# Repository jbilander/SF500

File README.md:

# SF500
Spitfire 500, A low-end 14 MHz Accelerator with IDE and 4/8 MB fast RAM for the Amiga 500.
***
Heavily inspired by Matthias Heinrichs' CDTV-RAM-IDE board. Many thanks to Matze for sharing his work and letting me open source this project.

https://gitlab.com/MHeinrichs/CDTV-RAM-IDE/

Please note, if you are going to build boards and sell for profit, you will need a consent from Matthias and also from Oliver Kastl if you are going to bundle this software http://aminet.net/package/disk/misc/oktapus with the hardware (ROM-chip).

***

    Board is four layers:
    
    signal (with 3V3-zone)
    power plane (GND)
    power plane (VCC)
    signal

***

Rev. 1B installed in an A500. The 7/14 MHz switch can be easily accessed if hanging out the sidecar port opening of the A500 case. This switch can also be switched while the machine is running.

***

***

Videos: <br /><br />
https://drive.google.com/file/d/1c2K9_kcEqxMMBJBd1aELfbt1fV5XXoU6/view?usp=sharing

SysInfo tests running _oktagon.device_ on WB 1.3 on KS 1.3: <br />
https://drive.google.com/file/d/1rewl8bivpIMPoLze_-Y7_mGYqzTiX6ET/view?usp=sharing

Cold boot running _oktagon.device_ and WB 1.3 on KS 1.3: <br />
https://drive.google.com/file/d/1MFdxnaCo8lNMqMQ6eJMtNUMSsBB8mtb-/view?usp=sharing

Cold boot running _scsi.device v109.3_  (oktapussy) and ClassicWB 3.1 (with 1.3 theme) on KS 3.1: <br />
https://drive.google.com/file/d/1IrmWWG6SJgc65BBj8jGnHebKbp6LAcYa/view?usp=sharing

***

The CPU and the speed-select switch clears the A500 keyboard nicely when installed. Also the CF- or SD-card adapter clears the ROM-chip nicely.

***

***

### Performance

14 MHz and JP3 Open (scsi.device v109.3):

<br />
<br />

14 MHz and JP3 Closed (oktagon.device v6.10):

***

Keep in mind Kickstart 1.3 does not have FFS (Fast File System) in ROM, 
so in order to use FFS with 1.3 make a small boot-partition (e.g. ~200 MB) and format it DOS\1, 
not International (DOS\3) or DirCache (DOS\5), and not OFS (DOS\0). For KS 3.1 I would format it FFS International (DOS\3) or perhaps use PFS3. <br /><br />
https://en.wikipedia.org/wiki/Amiga_Fast_File_System <br />

Also, do not forget to set the MaxTransfer to _0x1fe00_ and hit Enter button after typing, then save the setting. This applies to all versions except the new KS 3.2

<br />
<br />
Disk's partition and filesystem information should now be stored in the RDB (Rigid Disk Block)
for autoboot to work under WB 1.3 with oktagon.device. 
To install WB 1.3: Copy all content of the WB 1.3 floppy to the newly formatted Drive.

***

### How to Build:

The ROM image to burn to the AM29F040B-70JC chip can be downloaded from here: <br />
https://gitlab.com/MHeinrichs/CDTV-RAM-IDE/-/blob/master/Prog/ATOKTACOMBINED.rom-512.bin

The 64 KB ROM under _Releases_ is a combined ROM I made with the instructions from the textfile [EPROM-Hack_english.txt](https://github.com/jbilander/SF500/blob/main/EPROM-Hack_english.txt) in this repo (also available in German).
It is 060-compatible too, not that it makes any difference for this accelerator that uses a 68000 or 68010 CPU.

Burning any of the two ROM:s above will work with this Accelerator (SF500).

The last version of the Oktagon2008 from BSC is 6.12 - but still reports as 6.10. As far as I know, only the boot code has changed to be compatible with the 68060. The actual driver is still 6.10.

Remember to Program the chip BEFORE you solder it down to the PCB. Do not byteswap if you are using a TL866II-Plus or similar programmer on Windows/Intel-arch, these parts are 8-bit so there is no concept of byte swapping.

***

Soldering: Start with all the surface mounts and then TH. I usually start with the Voltage regulator and verify the 3V3. Then the CPLD and verify JTAG-connection, doing a boundary scan with ISE-Impact. No need to solder a pin header to the JTAG connector on the PCB, just hold the connector in position and press gently. It should also be possible to use a Raspberry Pi and the program _xc3sprog_. Optionally you can put 10k or 4.7k pull-ups on R10-R12 (TMS,TDI,TCK) if you have problems connecting to the CPLD, those are 3V3 pull-ups so shouldn't damage anything using GPIO from a RPi. VCC is +5V and can be supplied through a typical usb phone-charger or similar, check polarity BEFORE you plug it in.

***

<br />

***

Using some kapton tape can help to hold the chip in place while tacking it down to get everything aligned properly. For the ROM-chip I pre-tin the pads and then use hot air rework station to solder it in place.

***

<br />

***

When all the surface mount components are done it's time for the TH-pins. I use an old 68k CPU as a jig and a piece of pin strip on the other side to align the pins while soldering them in position. Press ontop the CPU somewhat at the same time when soldering for a great result.

***

***

I used a 1.2mm thick PCB as a spacer while soldering the 44-pin IDE connector in place. This because it'll clear the Kickstart ROM chip better if the connector and hence the adapter is positioned a little higher up. The 44-pinout on the PCB is deliberately flipped/designed so that you can plug the CF or SD-adapter directly to the angled-connector the "right" way, no ribbon cable and no buffering is used.

***

<br />

***

The final result. The mini-slide switch can optionally be soldered directly to the PCB if you prefer it that way. Only two pins are actually used, it's a normal two pin jumper with default pull-up, the third pin/hole is not connected and is only there to allow for soldering the mini-slide switch directly onto the PCB.

***

***

Programming can now be done either this way...

***

<br />

***

...or like in picture below...it requires the Amiga PSU to be turned ON to provide +5V to the Accelerator, do not connect any external +5V here:

***

***

Jumpers:

    /CFGIN = This jumper is to activate autoconfig (active low with 1k pull-down resistor R3). No jumper here means no RAM nor IDE will be autoconfigured. 
    SW1 = CPU speed toggle between 7 or 14 MHz, default 10k pull-up means 14 MHz
    JP2 = Selects between 4 or 8 MB fast ram autoconfig, 8 MB requires U7,U8 populated too.
    JP3 = Selects between IDE driver oktagon.device or scsi.device_v109.3 (oktapussy)
    JP4 = Selects between Autoboot or Not, jumper Closed means autoconfigure will not load the ROM-vector (the JP3-selected driver).

***

Synthesis Summary:

Zipped JED-file (_main_top.jed_) available under _Releases_

New firmware released 2021-12-22 that supports DMA from A590, available under _Releases_

***

### SF500 and A590
With the updated firmware it's now possible to use an A590 (on the A500 expansion edge) togheter with a SF500.
<br />
You will need to solder/connect a jumper-wire from the CFGOUT-goldfinger-pad and run it to the CFGIN-pin on the SF500. This will asure that there will be no conflict during AutoConfig cycles. They will be daisy-chained meaning the A590 configures first and the SF500 is second in line.

***

Having the A590 jumper set to enable onboard memory (2MB in picures below) is not optimal in this case since that memory will automatically be used first by the system. You will have to set the jumper (JP2) to _ON_ (4MB) on the SF500 in this scenario but as you can see only 0.84 mips here:

***

In this case it's much better to set the A590 jumper to _Amnesia_ and hence "only" use the 4MB or 8MB from the SF500. Don't worry the A590 can then DMA (Direct Memory Access) into that memory:

***

***

With the SF500 set to _Amnesia_ we get the full performance at 14 MHz and we can use the Hard Drive in the A590 either to boot from or just as a second harddrive for storage or backup (this depends on boot prio setting). Both the Oktagon.device and the Oktapussy scsi.device can co-exist with the A590 driver. As you can see the oktapussy driver takes the name _2nd_ scsi device here:

***

<br />

***

Changing boot priority in HDToolBox let us select which drive to boot from. Please note, I used prio 10 here but if you still want the DF0 floppy drive as the first device (you probably will) then you can't put in a number above 5. Keep it below 5 since DF0 has boot priority 5 by default, this was just for testing, remember to press Enter after entering the new value in the box and then hit the _Save Changes to Drive_ button before you do a reboot.

***

A short video showing boot from A590 in _Amnesia_ mode and copying a 2.2 MB file from the SF500 IDE drive to the A590 XT drive. <br /><br />
https://drive.google.com/file/d/1oLW0H9GmMaRv7rbYKLQVwRg4RvrDyU3E/view?usp=sharing
<br /><br />
Here a short video booting from the SF500 IDE drive (with higher boot prio set) than the A590 (still in _Amnesia_ mode). The A590 harddrive is automatically mounted and available to the system after startup:<br /><br />
https://drive.google.com/file/d/13qs9DawRrVdHNif9vCZlh3xlq8YgDj_f/view?usp=sharing

***

BOM Rev. 1B
---------
Position  | Name/Value   | Package | Notes
-|-|-|-|
U1 | 64Pcs socket pins for Round Plug 0.5mm Diameter | 100Pcs | IC Leads Receptacle, gold or nickel plated, used as TH Pin Header. https://www.aliexpress.com/item/1005002830101899.html
U2 | CPU Socket, 2 x 32 Female Pin Header 2.54mm pitch | 2 x Single Row 40Pin | Round Female Pin Header gold or nickel plated machined pins.
U3 | Voltage Regulator 3.3V, LM1117-3.3 or AMS1117-3.3 | SOT-223 | 3.3V 1A Low Drop-Out (LDO) Voltage regulator.
U4 | NB3N502 - 14 MHz to 190 MHz PLL Clock Multiplier | SOIC-8 | PLL with CLKOUT and at the same time output the input aligned reference clock signal (REF).
U5-U6 | 2 x CY62167G-45ZXI or 2 x CY62167ELL-45ZXI | 48-pin TSOP-I configurable as 1M × 16 or 2M × 8 SRAM |  First 4 MB. Cost $3 / Pcs from here https://www.aliexpress.com/item/1005003256658439.html (verified ok)
U7-U8 | 2 x CY62167G-45ZXI or 2 x CY62167ELL-45ZXI | | (Optional) Second 4 MB.
U9 | XC95144XL-TQ100 | TQFP-100_14x14mm_P0.5mm | IC Xilinx CPLD 144MC 10NS 100TQFP, XC95144XL-10TQG100C
U10 | 29F040 or 29F010 | PLCC-32_11.4x14.0mm_P1.27mm | e.g. AM29F040B-70JC or AS29CF010-55CCIN
U11 | 74HCT2G14 | TSOP-6 | Dual inverting Schmitt trigger
R1 | 10k | 1206 | /VPA Pull-up resistor
R2 | 10k | 1206 | JP2 Pull-up resistor (P74)
R3 | 1k | 1206 | /CFGIN Pull-down resistor (P70)
R4 | 33 Ohm or 0 Ohm | 1206 | (Optional) /CFGOUT series resistor (P68)
R5 | 10k | 1206 | JP3 Pull-up resistor (Line A15 ROM)
R6 | 4.7k | 1206 | IDE_IORDY Pull-up resistor (P12)
R7 | 1k | 1206 | IDE_IRQ Pull-down resistor (P27)
R8 | 4.7k | 1206 | /AS_CPU Pull-up resistor (P79)
R9 | 1k | 1206 | /DTACK_CPU Pull-up resistor (P13)
R10 | 4.7k or 10k | 0805 | (Optional) TMS 3.3V Pull-up resistor (P47)
R11 | 4.7k or 10k | 0805 | (Optional) TDI 3.3V Pull-up resistor (P45)
R12 | 4.7k or 10k | 0805 | (Optional) TCK 3.3V Pull-up resistor (P48)
R13 | 10k | 0805 | SW1 Pull-up resistor debounce circuit (P76)
R14 | 10k | 0805 | resistor in (RC) debounce circuit
R15 | 10k | 1206 | JP4 Pull-up (P67)
R16 | 4.7k or 10k | 0805 | (Optional) CFGIN Pull-up (P70)
C1 | 10uF | 1206 | capacitor for Voltage regulator
C2 | 10uF | 1206 | capacitor for Voltage regulator
C3 | 0.1uF = 100nF | 0805 | capacitor for Voltage regulator
C4 | 0.1uF = 100nF | 0805 | decoupling capacitor for U4 (PLL)
C5-C6 | 0.1uF = 100nF | 0805 | decoupling capacitors for U5-U6 (first 2 x SRAM)
C7-C8 | 0.1uF = 100nF | 0805 | decoupling capacitors for U7-U8 (if populated, second 2 x SRAM)
C9-C12 | 0.1uF = 100nF | 0805 | decoupling capacitors for U9 (CPLD)
C13 | 10uF | 1206 | capacitor for VCC-pin
C14 | 10uF | 1206 | capacitor for IDE VCC-pin
C15 | 0.1uF = 100nF | 0805 | decoupling capacitor for U10 (ROM)
C16 | 0.1uF = 100nF | 0805 | capacitor in (RC) debounce circuit (SW1)
C17 | 0.1uF = 100nF | 0805 | decoupling capacitor for U11 (Schmitt trigger inverter)
J1 | JTAG Pin Header 2.54mm pitch | Single row 6pin | (Optional) Pressing JTAG-header pins against holes while programming is enough.
J2 | External Pin Header 2.54mm pitch | Single row 5pin angled or straight | 2.54mm Jumper on CFGIN-pin needed for enable Autoconfig unless daisy chained.
SW1 (J3) | 3Pin Header 2.54mm pitch | Single row 3pin | Pin header with jumper select 7/14MHz or On-Off mini slide switch SS12D00 3pin 1P2T 2 Position toggle switch. Handle length: 3mm-6mm
J4 | 2.0mm Pitch Right Angle IDE-socket | Double Row (2 x 22) Female 44pin header socket | 2 x 25 or 2 x 40, pull pin 45, 46 using a plier and cut with a hacksaw = Pin header 2 x 22. https://www.aliexpress.com/item/4001286548060.html

***

Happy Hackin' 

***

[![CC BY-SA 4.0][cc-by-sa-shield]][cc-by-sa]

This work is licensed under a
[Creative Commons Attribution-ShareAlike 4.0 International License][cc-by-sa].

[![CC BY-SA 4.0][cc-by-sa-image]][cc-by-sa]

[cc-by-sa]: http://creativecommons.org/licenses/by-sa/4.0/
[cc-by-sa-image]: https://licensebuttons.net/l/by-sa/4.0/88x31.png
[cc-by-sa-shield]: https://img.shields.io/badge/License-CC%20BY--SA%204.0-lightgrey.svg

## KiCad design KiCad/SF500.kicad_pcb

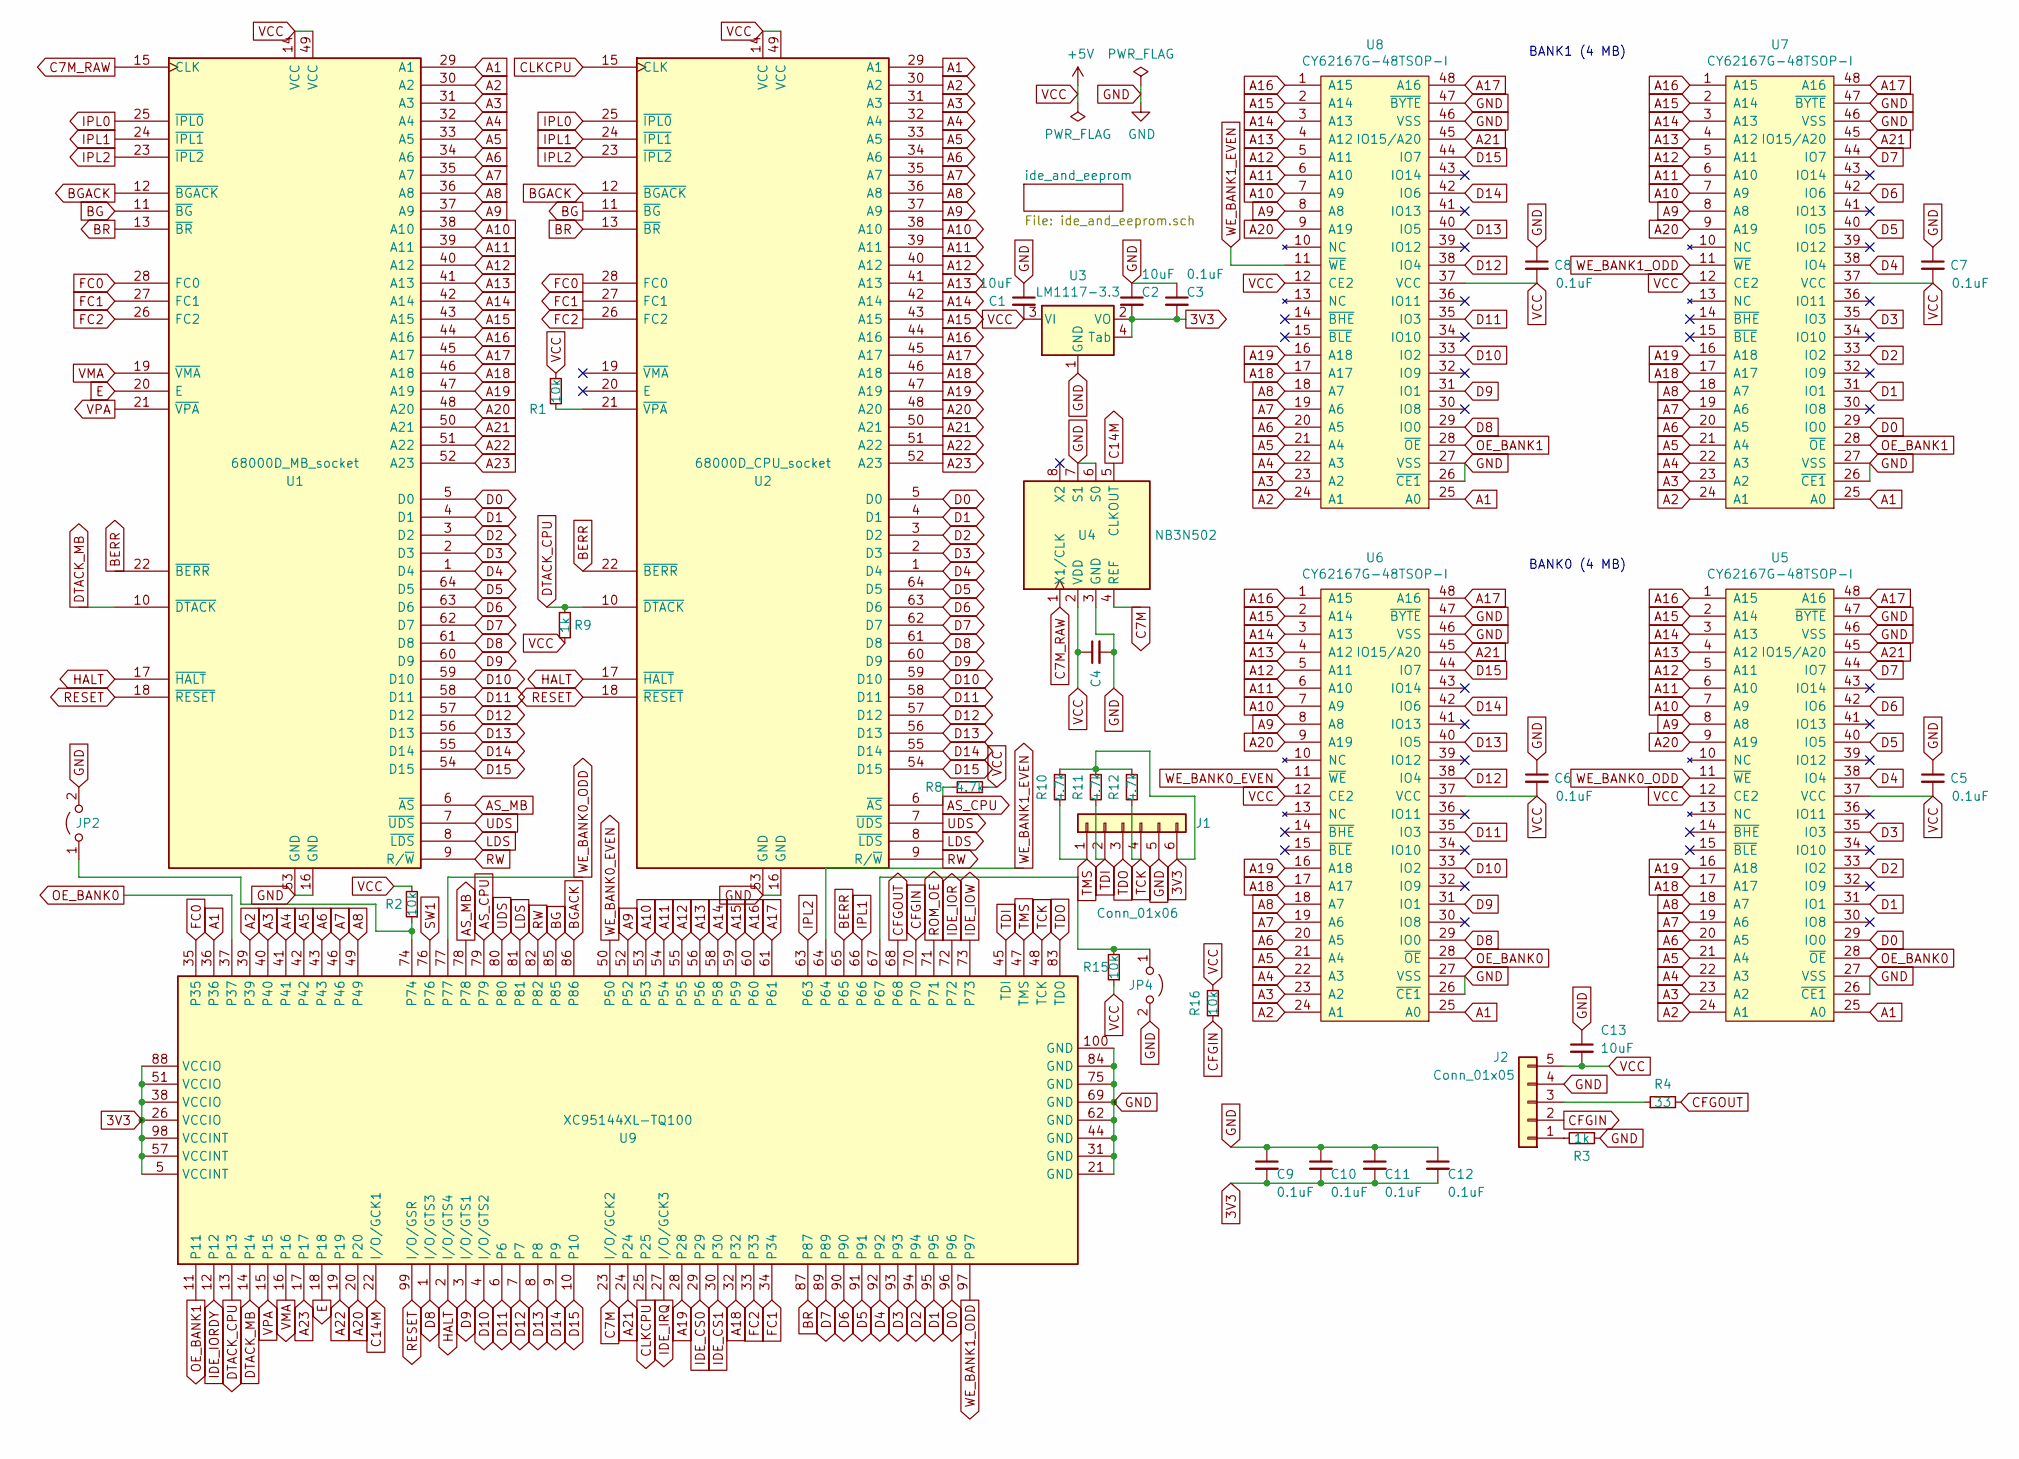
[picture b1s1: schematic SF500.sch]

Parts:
C1, C2, C13: 10uF; C_1206_3216Metric_Pad1.42x1.75mm_HandSolder
C3, C5, C6, C7, C8, C9, C10, C11, C12: 0.1uF; C_0805_2012Metric_Pad1.15x1.40mm_HandSolder
C4: 100nF; C_0805_2012Metric_Pad1.15x1.40mm_HandSolder
J1: Conn_01x06; PinHeader_1x06_P2.54mm_Vertical
J2: Conn_01x05; PinHeader_1x05_P2.54mm_Horizontal
JP2, JP4: Jumper_2_Open; PinHeader_1x02_P2.54mm_Vertical
R1, R2, R15: 10k; R_1206_3216Metric_Pad1.42x1.75mm_HandSolder
R3, R9: 1k; R_1206_3216Metric_Pad1.42x1.75mm_HandSolder
R4: 33; R_1206_3216Metric_Pad1.42x1.75mm_HandSolder
R8: 4.7k; R_1206_3216Metric_Pad1.42x1.75mm_HandSolder
R10, R11, R12: 4.7k; R_0805_2012Metric_Pad1.15x1.40mm_HandSolder
R16: 10k; R_0805_2012Metric_Pad1.15x1.40mm_HandSolder
U1: 68000D_MB_socket; DIP-64_W22.86mm_LongPads
U2: 68000D_CPU_socket; DIP-64_W22.86mm_LongPads
U3: LM1117-3.3; SOT-223
U4: NB3N502; SOIC-8_3.9x4.9mm_P1.27mm
U5, U6, U7, U8: CY62167G-48TSOP-I; TSOP-I-48_18.4x12mm_P0.5mm
U9: XC95144XL-TQ100; TQFP-100_14x14mm_P0.5mm

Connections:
3V3: C2.2, C3.2, C9.2, C10.2, C11.2, C12.2, J1.6, R10.1, R11.1, R12.1, U3.2 (VO), U3.4 (Tab), U9.5 (VCCINT), U9.26 (VCCIO), U9.38 (VCCIO), U9.51 (VCCIO), U9.57 (VCCINT), U9.88 (VCCIO), U9.98 (VCCINT)
A1: U1.29 (A1), U2.29 (A1), U5.25 (A0), U6.25 (A0), U7.25 (A0), U8.25 (A0), U9.36; also elsewhere on the board
A2: U1.30 (A2), U2.30 (A2), U5.24 (A1), U6.24 (A1), U7.24 (A1), U8.24 (A1), U9.39; also elsewhere on the board
A3: U1.31 (A3), U2.31 (A3), U5.23 (A2), U6.23 (A2), U7.23 (A2), U8.23 (A2), U9.40; also elsewhere on the board
A4: U1.32 (A4), U2.32 (A4), U5.22 (A3), U6.22 (A3), U7.22 (A3), U8.22 (A3), U9.41; also elsewhere on the board
A5: U1.33 (A5), U2.33 (A5), U5.21 (A4), U6.21 (A4), U7.21 (A4), U8.21 (A4), U9.42; also elsewhere on the board
A6: U1.34 (A6), U2.34 (A6), U5.20 (A5), U6.20 (A5), U7.20 (A5), U8.20 (A5), U9.43; also elsewhere on the board
A7: U1.35 (A7), U2.35 (A7), U5.19 (A6), U6.19 (A6), U7.19 (A6), U8.19 (A6), U9.46; also elsewhere on the board
A8: U1.36 (A8), U2.36 (A8), U5.18 (A7), U6.18 (A7), U7.18 (A7), U8.18 (A7), U9.49; also elsewhere on the board
A9: U1.37 (A9), U2.37 (A9), U5.8 (A8), U6.8 (A8), U7.8 (A8), U8.8 (A8), U9.52; also elsewhere on the board
A10: U1.38 (A10), U2.38 (A10), U5.7 (A9), U6.7 (A9), U7.7 (A9), U8.7 (A9), U9.53; also elsewhere on the board
A11: U1.39 (A11), U2.39 (A11), U5.6 (A10), U6.6 (A10), U7.6 (A10), U8.6 (A10), U9.54; also elsewhere on the board
A12: U1.40 (A12), U2.40 (A12), U5.5 (A11), U6.5 (A11), U7.5 (A11), U8.5 (A11), U9.55; also elsewhere on the board
A13: U1.41 (A13), U2.41 (A13), U5.4 (A12), U6.4 (A12), U7.4 (A12), U8.4 (A12), U9.56; also elsewhere on the board
A14: U1.42 (A14), U2.42 (A14), U5.3 (A13), U6.3 (A13), U7.3 (A13), U8.3 (A13), U9.58; also elsewhere on the board
A15: U1.43 (A15), U2.43 (A15), U5.2 (A14), U6.2 (A14), U7.2 (A14), U8.2 (A14), U9.59; also elsewhere on the board
A16: U1.44 (A16), U2.44 (A16), U5.1 (A15), U6.1 (A15), U7.1 (A15), U8.1 (A15), U9.60
A17: U1.45 (A17), U2.45 (A17), U5.48 (A16), U6.48 (A16), U7.48 (A16), U8.48 (A16), U9.61
A18: U1.46 (A18), U2.46 (A18), U5.17 (A17), U6.17 (A17), U7.17 (A17), U8.17 (A17), U9.32
A19: U1.47 (A19), U2.47 (A19), U5.16 (A18), U6.16 (A18), U7.16 (A18), U8.16 (A18), U9.28
A20: U1.48 (A20), U2.48 (A20), U5.9 (A19), U6.9 (A19), U7.9 (A19), U8.9 (A19), U9.20
A21: U1.50 (A21), U2.50 (A21), U5.45 (IO15/A20), U6.45 (IO15/A20), U7.45 (IO15/A20), U8.45 (IO15/A20), U9.24
A22: U1.51 (A22), U2.51 (A22), U9.19
A23: U1.52 (A23), U2.52 (A23), U9.17
AS_CPU: R8.1, U2.6 (~AS), U9.79
AS_MB: U1.6 (~AS), U9.78
BERR: U1.22 (~BERR), U2.22 (~BERR), U9.65
BG: U1.11 (~BG), U2.11 (~BG), U9.85
BGACK: U1.12 (~BGACK), U2.12 (~BGACK), U9.86
BR: U1.13 (~BR), U2.13 (~BR), U9.87
C7M: U4.4 (REF), U9.23 (I/O/GCK2)
C7M_RAW: U1.15 (CLK), U4.1 (X1/CLK)
C14M: U4.5 (CLKOUT), U9.22 (I/O/GCK1)
CFGIN: J2.2, R16.1, U9.70
CFGOUT: R4.2, U9.68
CLKCPU: U2.15 (CLK), U9.25
D0: U1.5 (D0), U2.5 (D0), U5.29 (IO0), U7.29 (IO0), U9.96; also elsewhere on the board
D1: U1.4 (D1), U2.4 (D1), U5.31 (IO1), U7.31 (IO1), U9.95; also elsewhere on the board
D2: U1.3 (D2), U2.3 (D2), U5.33 (IO2), U7.33 (IO2), U9.94; also elsewhere on the board
D3: U1.2 (D3), U2.2 (D3), U5.35 (IO3), U7.35 (IO3), U9.93; also elsewhere on the board
D4: U1.1 (D4), U2.1 (D4), U5.38 (IO4), U7.38 (IO4), U9.92; also elsewhere on the board
D5: U1.64 (D5), U2.64 (D5), U5.40 (IO5), U7.40 (IO5), U9.91; also elsewhere on the board
D6: U1.63 (D6), U2.63 (D6), U5.42 (IO6), U7.42 (IO6), U9.90; also elsewhere on the board
D7: U1.62 (D7), U2.62 (D7), U5.44 (IO7), U7.44 (IO7), U9.89; also elsewhere on the board
D8: U1.61 (D8), U2.61 (D8), U6.29 (IO0), U8.29 (IO0), U9.1 (I/O/GTS3); also elsewhere on the board
D9: U1.60 (D9), U2.60 (D9), U6.31 (IO1), U8.31 (IO1), U9.3 (I/O/GTS1); also elsewhere on the board
D10: U1.59 (D10), U2.59 (D10), U6.33 (IO2), U8.33 (IO2), U9.4 (I/O/GTS2); also elsewhere on the board
D11: U1.58 (D11), U2.58 (D11), U6.35 (IO3), U8.35 (IO3), U9.6; also elsewhere on the board
D12: U1.57 (D12), U2.57 (D12), U6.38 (IO4), U8.38 (IO4), U9.7; also elsewhere on the board
D13: U1.56 (D13), U2.56 (D13), U6.40 (IO5), U8.40 (IO5), U9.8; also elsewhere on the board
D14: U1.55 (D14), U2.55 (D14), U6.42 (IO6), U8.42 (IO6), U9.9; also elsewhere on the board
D15: U1.54 (D15), U2.54 (D15), U6.44 (IO7), U8.44 (IO7), U9.10; also elsewhere on the board
DTACK_CPU: R9.1, U2.10 (~DTACK), U9.13
DTACK_MB: U1.10 (~DTACK), U9.14
E: U1.20 (E), U9.18
FC0: U1.28 (FC0), U2.28 (FC0), U9.35
FC1: U1.27 (FC1), U2.27 (FC1), U9.34
FC2: U1.26 (FC2), U2.26 (FC2), U9.33
GND: C1.1, C2.1, C3.1, C4.2, C5.1, C6.1, C7.1, C8.1, C9.1, C10.1, C11.1, C12.1, C13.1, J1.5, J2.4, JP2.2 (B), JP4.2 (B), R3.1, U1.16 (GND), U1.53 (GND), U2.16 (GND), U2.53 (GND), U3.1 (GND), U4.3 (GND), U4.6 (S0), U4.7 (S1), U5.26 (~CE1), U5.27 (VSS), U5.46 (VSS), U5.47 (~BYTE), U6.26 (~CE1), U6.27 (VSS), U6.46 (VSS), U6.47 (~BYTE), U7.26 (~CE1), U7.27 (VSS), U7.46 (VSS), U7.47 (~BYTE), U8.26 (~CE1), U8.27 (VSS), U8.46 (VSS), U8.47 (~BYTE), U9.21 (GND), U9.31 (GND), U9.44 (GND), U9.62 (GND), U9.69 (GND), U9.75 (GND), U9.84 (GND), U9.100 (GND); also elsewhere on the board
HALT: U1.17 (~HALT), U2.17 (~HALT), U9.2 (I/O/GTS4)
IDE_CS0: U9.29; also elsewhere on the board
IDE_CS1: U9.30; also elsewhere on the board
IDE_IOR: U9.72; also elsewhere on the board
IDE_IORDY: U9.12; also elsewhere on the board
IDE_IOW: U9.73; also elsewhere on the board
IDE_IRQ: U9.27 (I/O/GCK3); also elsewhere on the board
IPL0: U1.25 (~IPL0), U2.25 (~IPL0)
IPL1: U1.24 (~IPL1), U2.24 (~IPL1), U9.66
IPL2: U1.23 (~IPL2), U2.23 (~IPL2), U9.63
LDS: U1.8 (~LDS), U2.8 (~LDS), U9.81
unnamed: J2.1, R3.2
unnamed: J2.3, R4.1
unnamed: JP2.1 (A), R2.1, U9.74
unnamed: JP4.1 (A), R15.2, U9.67
unnamed: R1.2, U2.21 (~VPA)
OE_BANK0: U5.28 (~OE), U6.28 (~OE), U9.37
OE_BANK1: U7.28 (~OE), U8.28 (~OE), U9.11
RESET: U1.18 (~RESET), U2.18 (~RESET), U9.99 (I/O/GSR); also elsewhere on the board
ROM_OE: U9.71; also elsewhere on the board
RW: U1.9 (R/~W), U2.9 (R/~W), U9.82
SW1: U9.76; also elsewhere on the board
TCK: J1.4, R12.2, U9.48 (TCK)
TDI: J1.2, R11.2, U9.45 (TDI)
TDO: J1.3, U9.83 (TDO)
TMS: J1.1, R10.2, U9.47 (TMS)
UDS: U1.7 (~UDS), U2.7 (~UDS), U9.80
VCC: C1.2, C4.1, C5.2, C6.2, C7.2, C8.2, C13.2, J2.5, R1.1, R2.2, R8.2, R9.2, R15.1, R16.2, U1.14 (VCC), U1.49 (VCC), U2.14 (VCC), U2.49 (VCC), U3.3 (VI), U4.2 (VDD), U5.12 (CE2), U5.37 (VCC), U6.12 (CE2), U6.37 (VCC), U7.12 (CE2), U7.37 (VCC), U8.12 (CE2), U8.37 (VCC); also elsewhere on the board
VMA: U1.19 (~VMA), U9.16
VPA: U1.21 (~VPA), U9.15
WE_BANK0_EVEN: U6.11 (~WE), U9.50
WE_BANK0_ODD: U5.11 (~WE), U9.77
WE_BANK1_EVEN: U8.11 (~WE), U9.64
WE_BANK1_ODD: U7.11 (~WE), U9.97

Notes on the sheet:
BANK0 (4 MB)
BANK1 (4 MB)

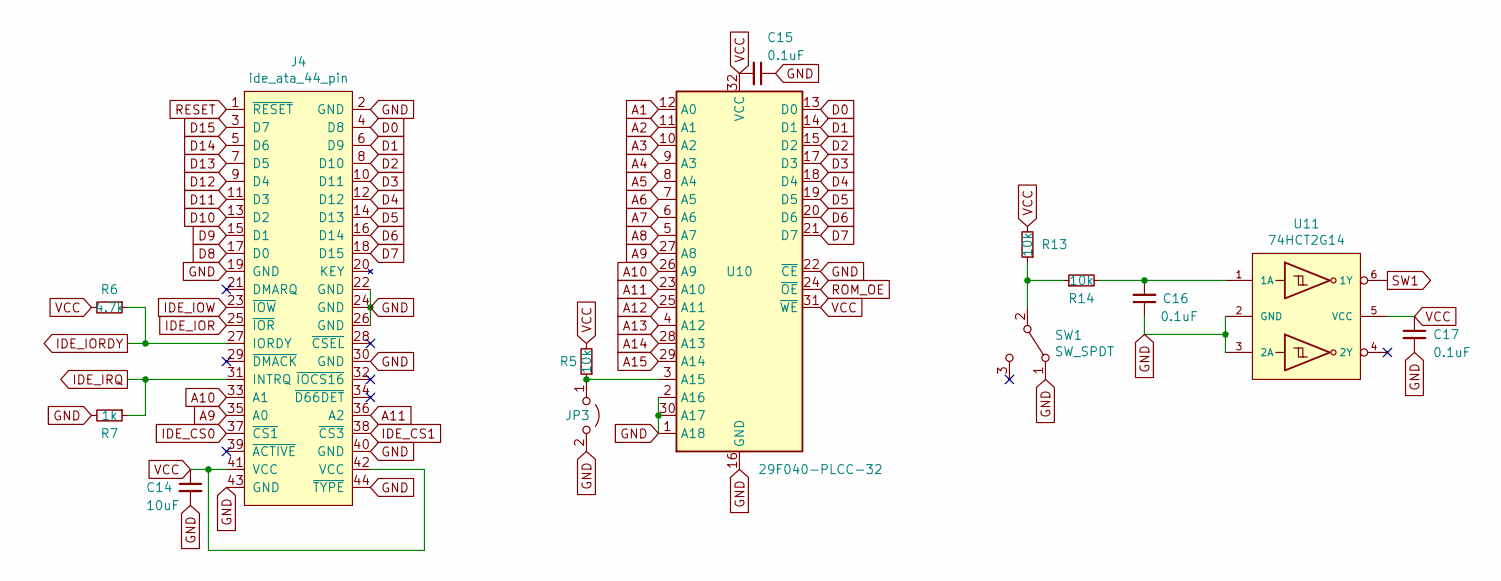
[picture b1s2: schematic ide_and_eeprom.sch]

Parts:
C14: 10uF; C_1206_3216Metric_Pad1.42x1.75mm_HandSolder
C15, C16, C17: 0.1uF; C_0805_2012Metric_Pad1.15x1.40mm_HandSolder
J4: ide_ata_44_pin; PinSocket_2x22_P2.00mm_Horizontal
JP3: Jumper_2_Open; PinHeader_1x02_P2.54mm_Vertical
R5: 10k; R_1206_3216Metric_Pad1.42x1.75mm_HandSolder
R6: 4.7k; R_1206_3216Metric_Pad1.42x1.75mm_HandSolder
R7: 1k; R_1206_3216Metric_Pad1.42x1.75mm_HandSolder
R13, R14: 10k; R_0805_2012Metric_Pad1.15x1.40mm_HandSolder
SW1: SW_SPDT; PinHeader_1x03_P2.54mm_Vertical
U10: 29F040-PLCC-32; PLCC-32_11.4x14.0mm_P1.27mm
U11: 74HCT2G14; TSOP-6_1.65x3.05mm_P0.95mm

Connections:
A1: U10.12 (A0); also elsewhere on the board
A2: U10.11 (A1); also elsewhere on the board
A3: U10.10 (A2); also elsewhere on the board
A4: U10.9 (A3); also elsewhere on the board
A5: U10.8 (A4); also elsewhere on the board
A6: U10.7 (A5); also elsewhere on the board
A7: U10.6 (A6); also elsewhere on the board
A8: U10.5 (A7); also elsewhere on the board
A9: J4.35 (A0), U10.27 (A8); also elsewhere on the board
A10: J4.33 (A1), U10.26 (A9); also elsewhere on the board
A11: J4.36 (A2), U10.23 (A10); also elsewhere on the board
A12: U10.25 (A11); also elsewhere on the board
A13: U10.4 (A12); also elsewhere on the board
A14: U10.28 (A13); also elsewhere on the board
A15: U10.29 (A14); also elsewhere on the board
D0: J4.4 (D8), U10.13 (D0); also elsewhere on the board
D1: J4.6 (D9), U10.14 (D1); also elsewhere on the board
D2: J4.8 (D10), U10.15 (D2); also elsewhere on the board
D3: J4.10 (D11), U10.17 (D3); also elsewhere on the board
D4: J4.12 (D12), U10.18 (D4); also elsewhere on the board
D5: J4.14 (D13), U10.19 (D5); also elsewhere on the board
D6: J4.16 (D14), U10.20 (D6); also elsewhere on the board
D7: J4.18 (D15), U10.21 (D7); also elsewhere on the board
D8: J4.17 (D0); also elsewhere on the board
D9: J4.15 (D1); also elsewhere on the board
D10: J4.13 (D2); also elsewhere on the board
D11: J4.11 (D3); also elsewhere on the board
D12: J4.9 (D4); also elsewhere on the board
D13: J4.7 (D5); also elsewhere on the board
D14: J4.5 (D6); also elsewhere on the board
D15: J4.3 (D7); also elsewhere on the board
GND: C14.2, C15.1, C16.1, C17.2, J4.2 (GND), J4.19 (GND), J4.22 (GND), J4.24 (GND), J4.26 (GND), J4.30 (GND), J4.40 (GND), J4.43 (GND), J4.44 (~TYPE), JP3.2 (B), R7.2, SW1.1 (A), U10.1 (A18), U10.2 (A16), U10.16 (GND), U10.22 (~CE), U10.30 (A17), U11.2 (GND), U11.3 (2A); also elsewhere on the board
IDE_CS0: J4.37 (~CS1); also elsewhere on the board
IDE_CS1: J4.38 (~CS3); also elsewhere on the board
IDE_IOR: J4.25 (~IOR); also elsewhere on the board
IDE_IORDY: J4.27 (IORDY), R6.1; also elsewhere on the board
IDE_IOW: J4.23 (~IOW); also elsewhere on the board
IDE_IRQ: J4.31 (INTRQ), R7.1; also elsewhere on the board
unnamed: C16.2, R14.2, U11.1 (1A)
unnamed: JP3.1 (A), R5.1, U10.3 (A15)
unnamed: R13.1, R14.1, SW1.2 (B)
RESET: J4.1 (~RESET); also elsewhere on the board
ROM_OE: U10.24 (~OE); also elsewhere on the board
SW1: U11.6 (1Y); also elsewhere on the board
VCC: C14.1, C15.2, C17.1, J4.41 (VCC), J4.42 (VCC), R5.2, R6.2, R13.2, U10.31 (~WE), U10.32 (VCC), U11.5 (VCC); also elsewhere on the board

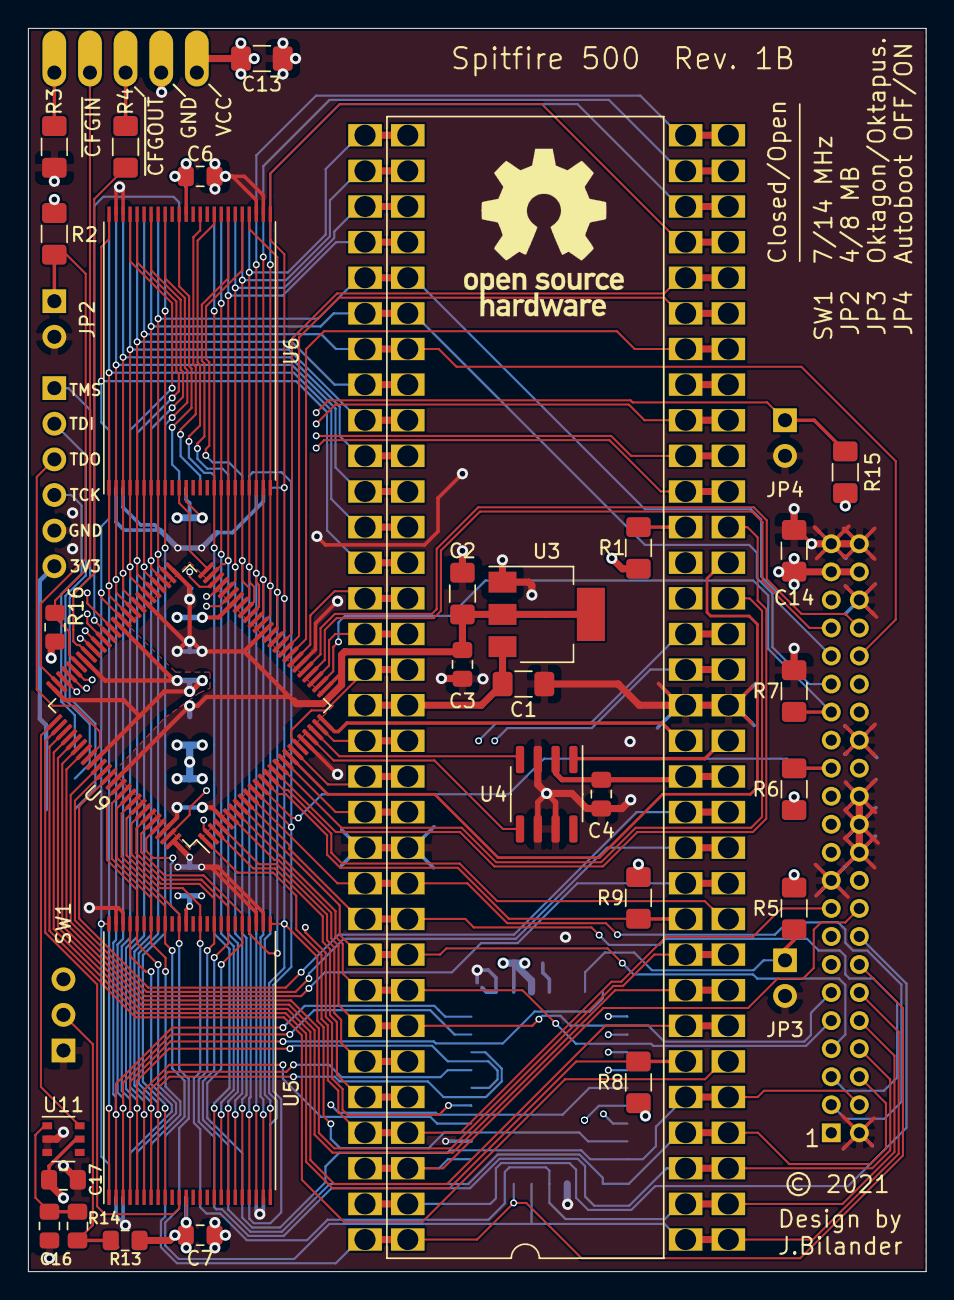
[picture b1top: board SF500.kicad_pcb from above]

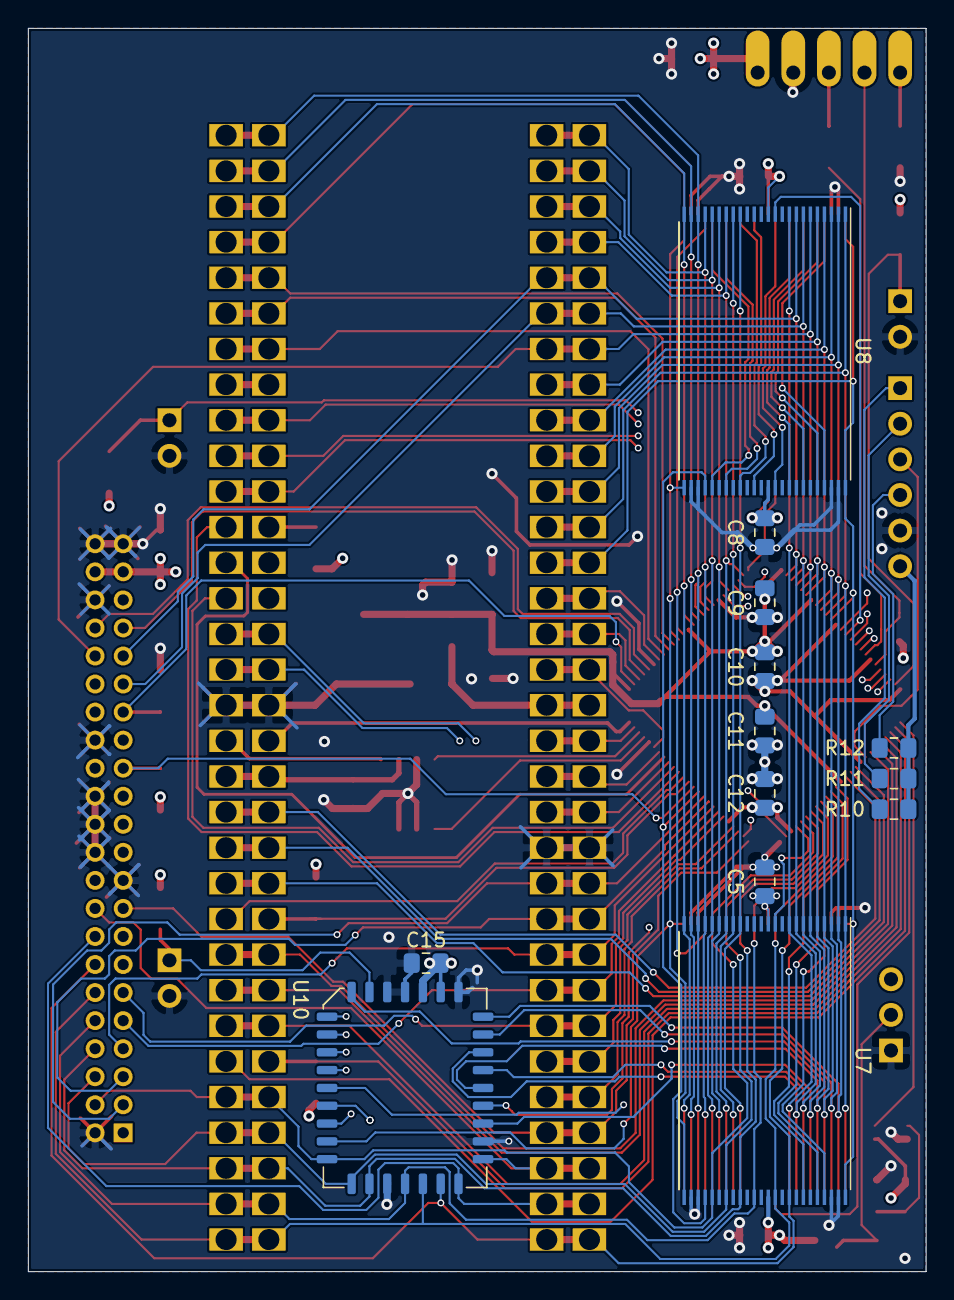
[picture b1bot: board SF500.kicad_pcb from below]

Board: 4 copper layers, 64.0 x 88.6 mm, 51 parts (13 on the bottom side), 96 nets.

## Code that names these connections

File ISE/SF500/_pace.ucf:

#PACE: Start of Constraints generated by PACE

#PACE: Start of PACE I/O Pin Assignments
NET "A12"  LOC = "P55"  ; 
NET "A13"  LOC = "P56"  ; 
NET "A_HIGH<16>"  LOC = "P60"  ; 
NET "A_HIGH<17>"  LOC = "P61"  ; 
NET "A_HIGH<18>"  LOC = "P32"  ; 
NET "A_HIGH<19>"  LOC = "P28"  ; 
NET "A_HIGH<20>"  LOC = "P20"  ; 
NET "A_HIGH<21>"  LOC = "P24"  ; 
NET "A_HIGH<22>"  LOC = "P19"  ; 
NET "A_HIGH<23>"  LOC = "P17"  ; 
NET "A_LOW<1>"  LOC = "P36"  ; 
NET "A_LOW<2>"  LOC = "P39"  ; 
NET "A_LOW<3>"  LOC = "P40"  ; 
NET "A_LOW<4>"  LOC = "P41"  ; 
NET "A_LOW<5>"  LOC = "P42"  ; 
NET "A_LOW<6>"  LOC = "P43"  ; 
NET "AS_CPU_n"  LOC = "P79"  ; 
NET "AS_MB_n"  LOC = "P78"  ; 
NET "C14M"  LOC = "P22" | BUFG = CLK ; 
NET "C7M"  LOC = "P23" | BUFG = CLK ; 
NET "CFGIN_n"  LOC = "P70"  ; 
NET "CFGOUT_n"  LOC = "P68"  ; 
NET "CLKCPU"  LOC = "P25"  ; 
NET "D<12>"  LOC = "P7"  ; 
NET "D<13>"  LOC = "P8"  ; 
NET "D<14>"  LOC = "P9"  ; 
NET "D<15>"  LOC = "P10"  ; 
NET "DTACK_CPU_n"  LOC = "P13" | NOREDUCE = TRUE ;
NET "DTACK_MB_n"  LOC = "P14"  ; 
NET "E"  LOC = "P18"  ; 
NET "FC<0>"  LOC = "P35"  ; 
NET "FC<1>"  LOC = "P34"  ; 
NET "FC<2>"  LOC = "P33"  ; 
NET "IDE_CS_n<0>"  LOC = "P29"  ; 
NET "IDE_CS_n<1>"  LOC = "P30"  ; 
NET "IDE_IOR_n"  LOC = "P72"  ; 
NET "IDE_IOW_n"  LOC = "P73"  ; 
NET "JP2"  LOC = "P74"  ; 
NET "JP4"  LOC = "P67"  ;
NET "LDS_n"  LOC = "P81"  ; 
NET "OE_BANK0_n"  LOC = "P37"  ; 
NET "OE_BANK1_n"  LOC = "P11"  ; 
NET "RESET_n"  LOC = "P99" | BUFG = SR ; 
NET "ROM_OE_n"  LOC = "P71"  ; 
NET "RW_n"  LOC = "P82"  ; 
NET "SW1"  LOC = "P76"  ; 
NET "UDS_n"  LOC = "P80"  ; 
NET "VMA_n"  LOC = "P16"  ; 
NET "VPA_n"  LOC = "P15"  ; 
NET "WE_BANK0_EVEN_n"  LOC = "P50"  ; 
NET "WE_BANK0_ODD_n"  LOC = "P77"  ; 
NET "WE_BANK1_EVEN_n"  LOC = "P64"  ; 
NET "WE_BANK1_ODD_n"  LOC = "P97"  ; 

#PACE: Start of PACE Area Constraints

#PACE: Start of PACE Prohibit Constraints

#PACE: End of Constraints generated by PACE

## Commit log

2021-05-13 added schematic pdf
2021-05-24 added files
2021-05-24 added verilog source files
2021-05-24 Update schematic pdf
2021-05-31 allow for dma
2021-06-07 implemented IDE
2021-06-11 deleted file accel.v
2021-06-11 code cleanup, removed unused IOs
2021-06-16 Removed unused pin assignments
2021-06-16 added license file
2021-06-16 added images
2021-06-16 added rev1b schematic
2021-06-16 Update pinout
2021-06-18 Updated pic
2021-07-01 Update pics
2021-08-31 modified image size
2021-08-31 deleted images
2021-09-01 added pics
2021-09-01 fixed image size
2021-09-02 Implemented Autoboot control by jumper setting (JP4), loading ROM-vector or not in Autoconfig
2021-09-02 added pic
2021-09-02 added KiCad files
2021-09-03 added Howto hack a combined AT-OKTA ROM that is 060 compatible too
2021-12-22 implemented DMA support for other busmaster e.g. A590 on expansion edge
2022-01-13 fixed modified symbol 68000D to reside in SF500.lib
2022-02-04 Update BOM with CY62167ELL-45ZXI verified working

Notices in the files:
KiCad/SF500.kicad_pcb:
© 2021
